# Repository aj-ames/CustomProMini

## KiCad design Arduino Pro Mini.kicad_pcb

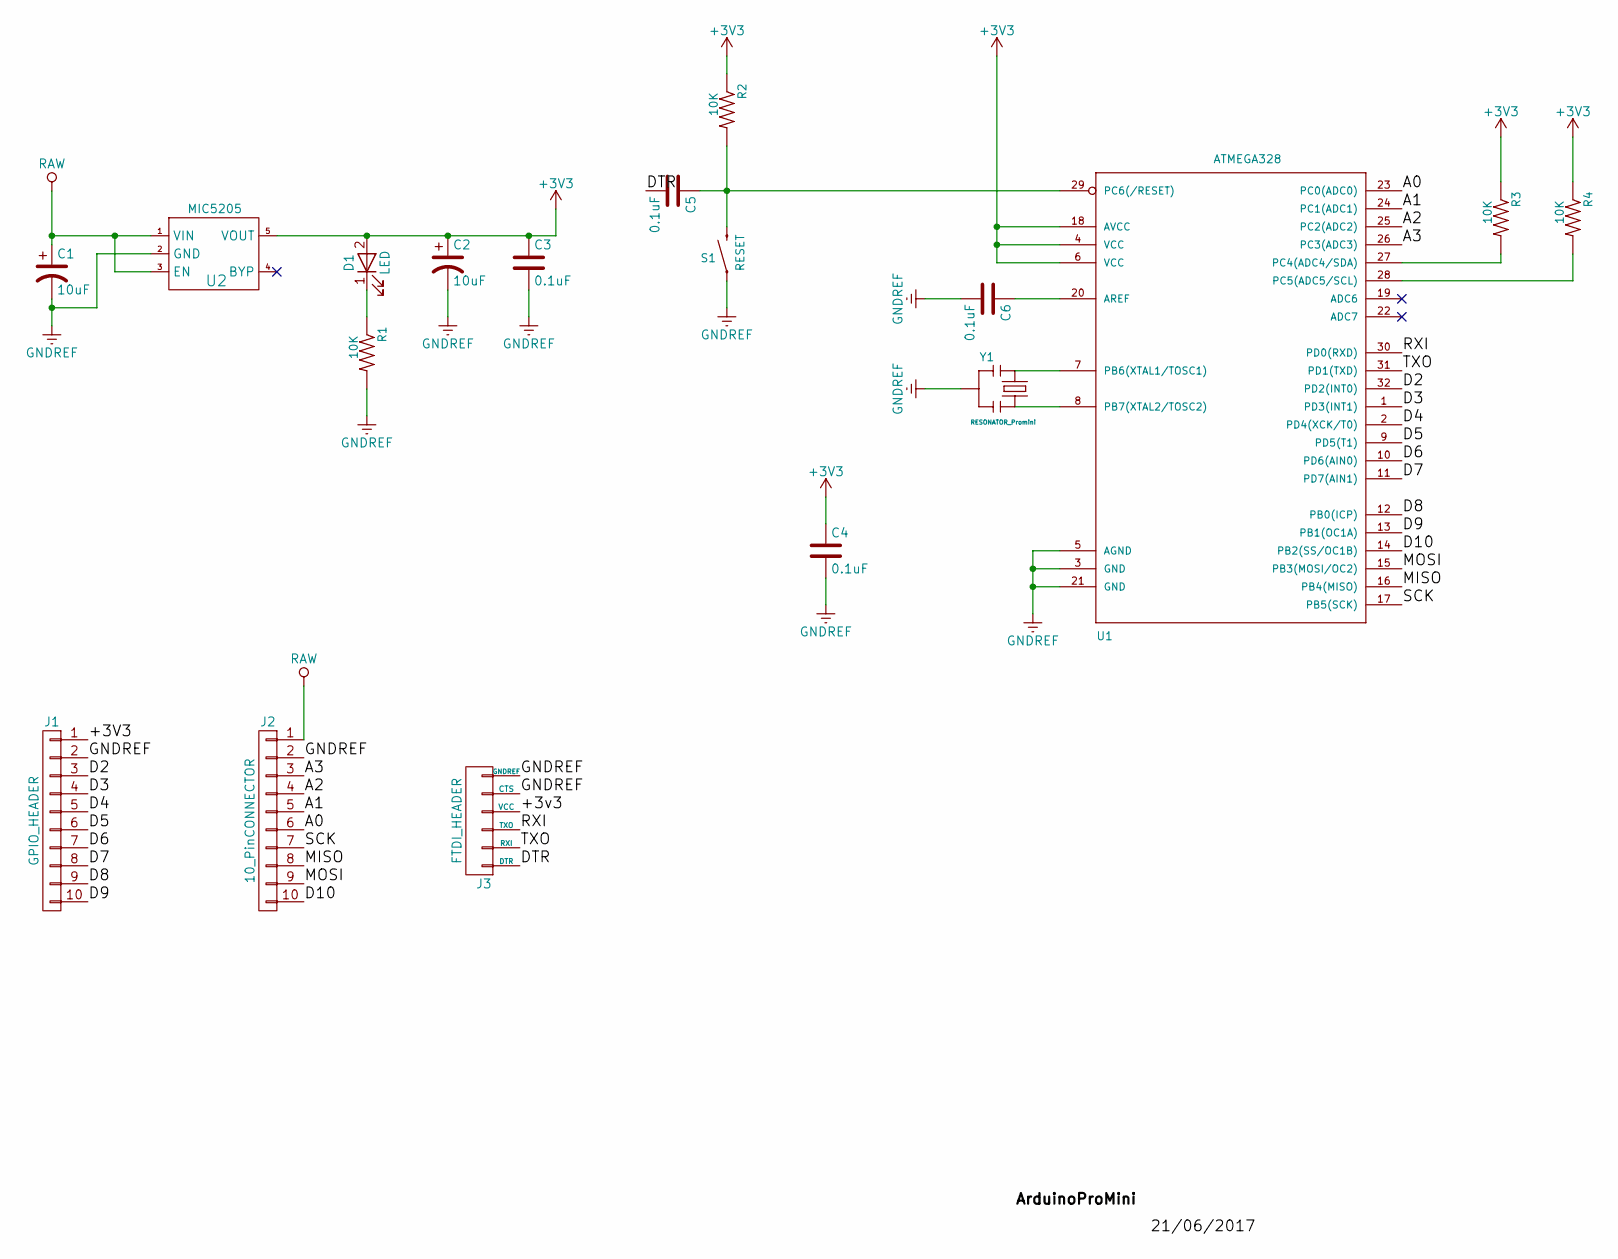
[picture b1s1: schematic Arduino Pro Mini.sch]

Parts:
C1, C2: 10uF; Capacitor_0603
C3, C4: 0.1uF; Capacitor_0402
C5, C6: 0.1uF; Capacitor_0603
D1: LED; LED_0603
J1: GPIO_HEADER; Pin_Header_1X10
J2: 10_PinCONNECTOR; Pin_Header_1X10
J3: FTDI_HEADER; Pin_Header_1X06
R1: 10K; Capacitor_0402
R2, R3, R4: 10K; Resistor_0603
S1: RESET; RESET SWITCH
U1: ATMEGA328; ATMEGA328_TQFP32-08
U2: MIC5205
Y1: RESONATOR_Promini; RESONATOR-SMD

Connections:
+3V3: C2.1, C3.1, C4.1, D1.2 (A), J1.1, J3.4 (VCC), R2.1, R3.1, R4.1, U1.4 (VCC), U1.6 (VCC), U1.18 (AVCC), U2.5 (VOUT)
/A0: J2.6, U1.23 (PC0(ADC0))
/A1: J2.5, U1.24 (PC1(ADC1))
/A2: J2.4, U1.25 (PC2(ADC2))
/A3: J2.3, U1.26 (PC3(ADC3))
/D2: J1.3, U1.32 (PD2(INT0))
/D3: J1.4, U1.1 (PD3(INT1))
/D4: J1.5, U1.2 (PD4(XCK/T0))
/D5: J1.6, U1.9 (PD5(T1))
/D6: J1.7, U1.10 (PD6(AIN0))
/D7: J1.8, U1.11 (PD7(AIN1))
/D8: J1.9, U1.12 (PB0(ICP))
/D9: J1.10, U1.13 (PB1(OC1A))
/D10: J2.10, U1.14 (PB2(SS/OC1B))
/DTR: C5.2, J3.1 (DTR)
/MISO: J2.8, U1.16 (PB4(MISO))
/MOSI: J2.9, U1.15 (PB3(MOSI/OC2))
/RXI: J3.3 (TXO), U1.30 (PD0(RXD))
/SCK: J2.7, U1.17 (PB5(SCK))
/TXO: J3.2 (RXI), U1.31 (PD1(TXD))
GNDREF: C1.2, C2.2, C3.2, C4.2, C6.2, J1.2, J2.2, J3.5 (CTS), J3.6 (GNDREF), R1.2, S1.1, U1.3 (GND), U1.5 (AGND), U1.21 (GND), U2.2 (GND), Y1.2
unnamed: C5.1, R2.2, S1.2, U1.29 (PC6(/RESET))
unnamed: C6.1, U1.20 (AREF)
unnamed: D1.1 (K), R1.1
unnamed: R3.2, U1.27 (PC4(ADC4/SDA))
unnamed: R4.2, U1.28 (PC5(ADC5/SCL))
unnamed: U1.7 (PB6(XTAL1/TOSC1)), Y1.1
unnamed: U1.8 (PB7(XTAL2/TOSC2)), Y1.3
RAW: C1.1, J2.1, U2.1 (VIN), U2.3 (EN)

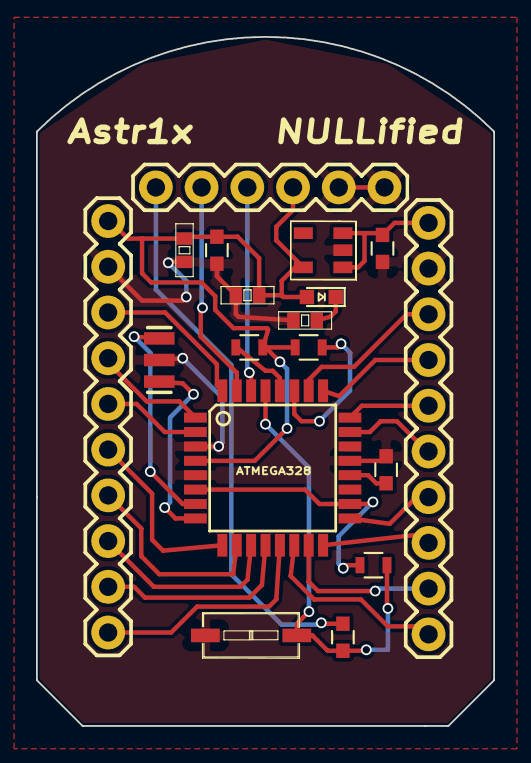
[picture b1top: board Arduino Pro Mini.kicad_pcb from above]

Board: 2 copper layers, 25.4 x 38.3 mm, 18 parts (0 on the bottom side), 29 nets.
